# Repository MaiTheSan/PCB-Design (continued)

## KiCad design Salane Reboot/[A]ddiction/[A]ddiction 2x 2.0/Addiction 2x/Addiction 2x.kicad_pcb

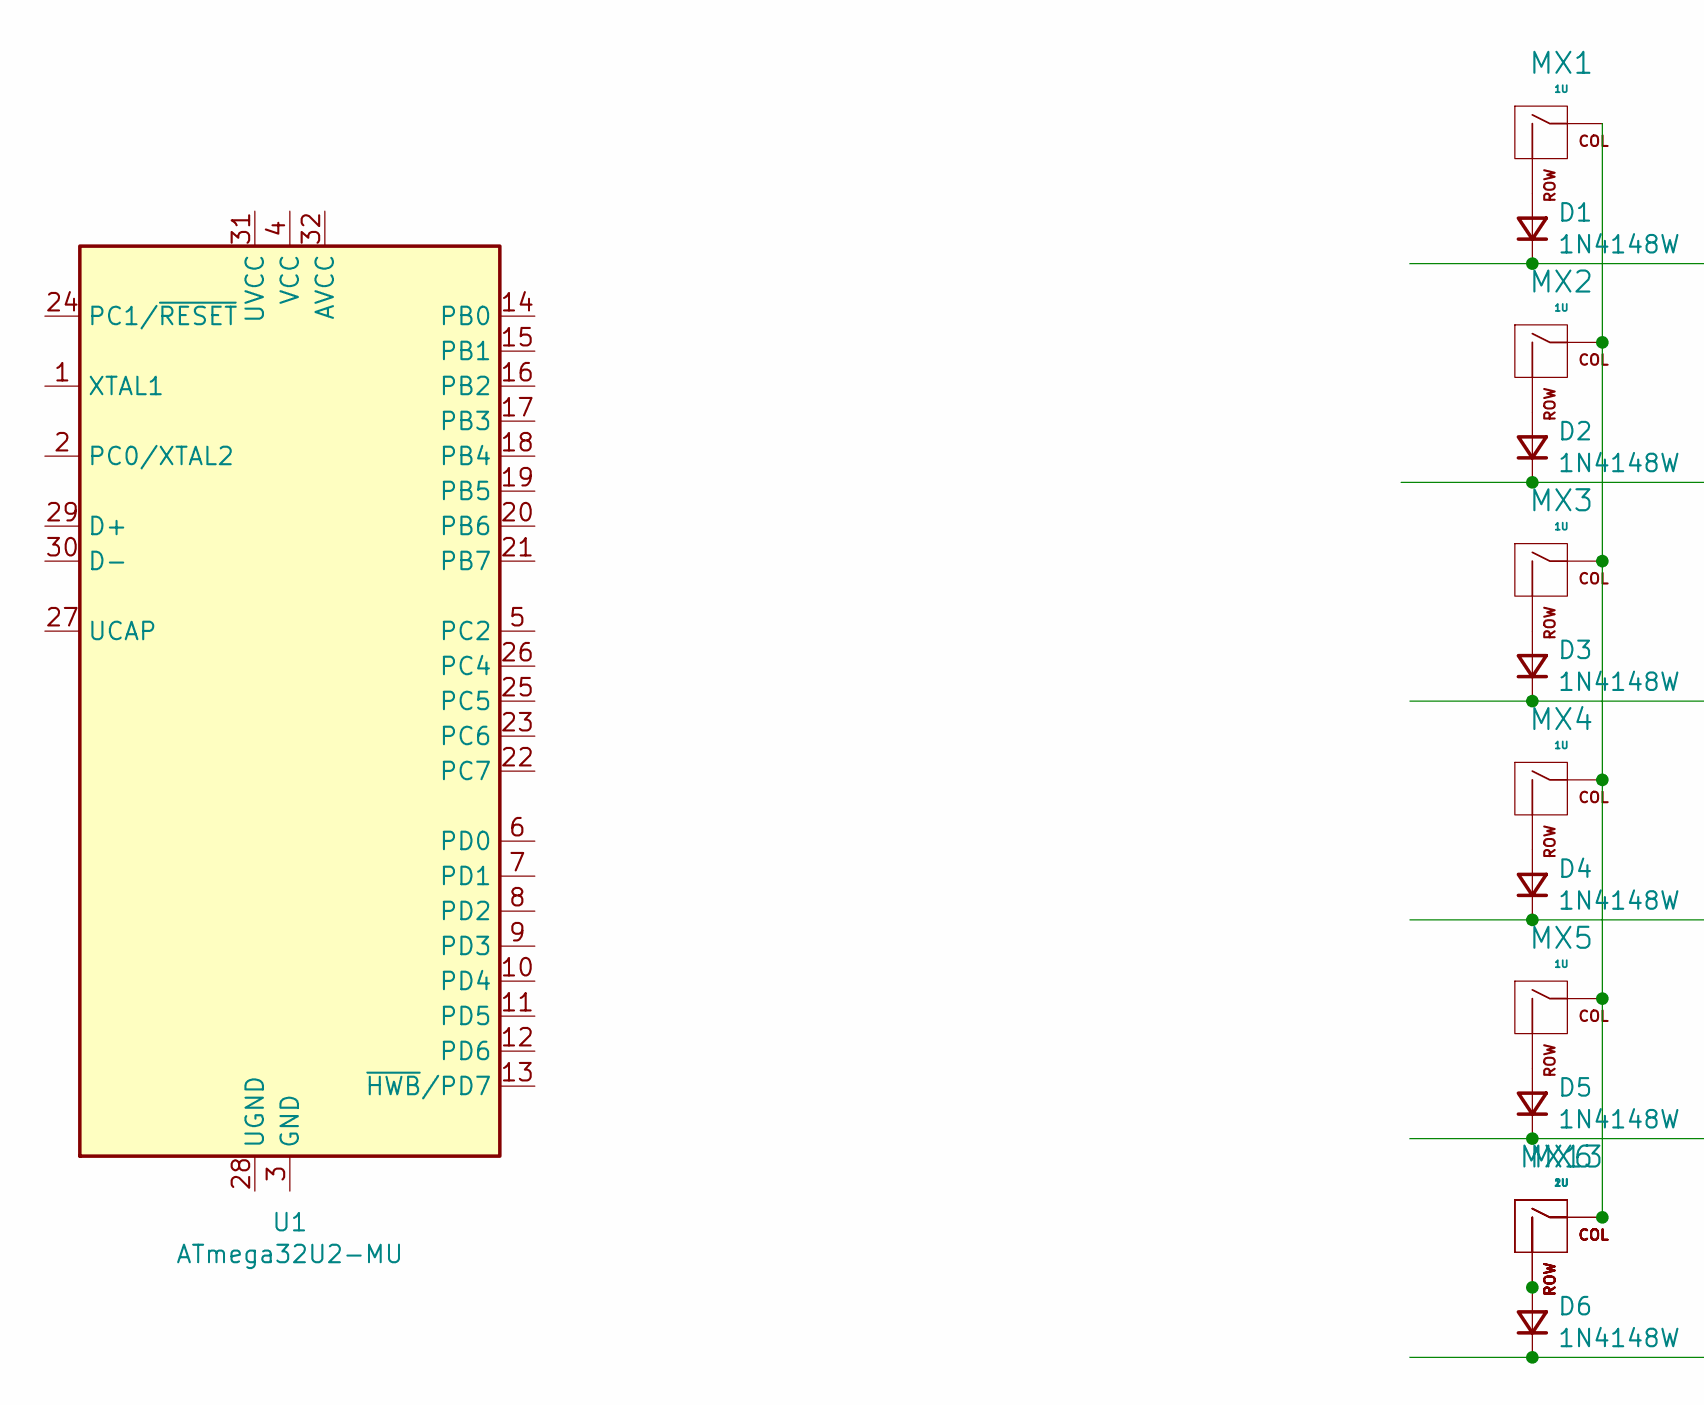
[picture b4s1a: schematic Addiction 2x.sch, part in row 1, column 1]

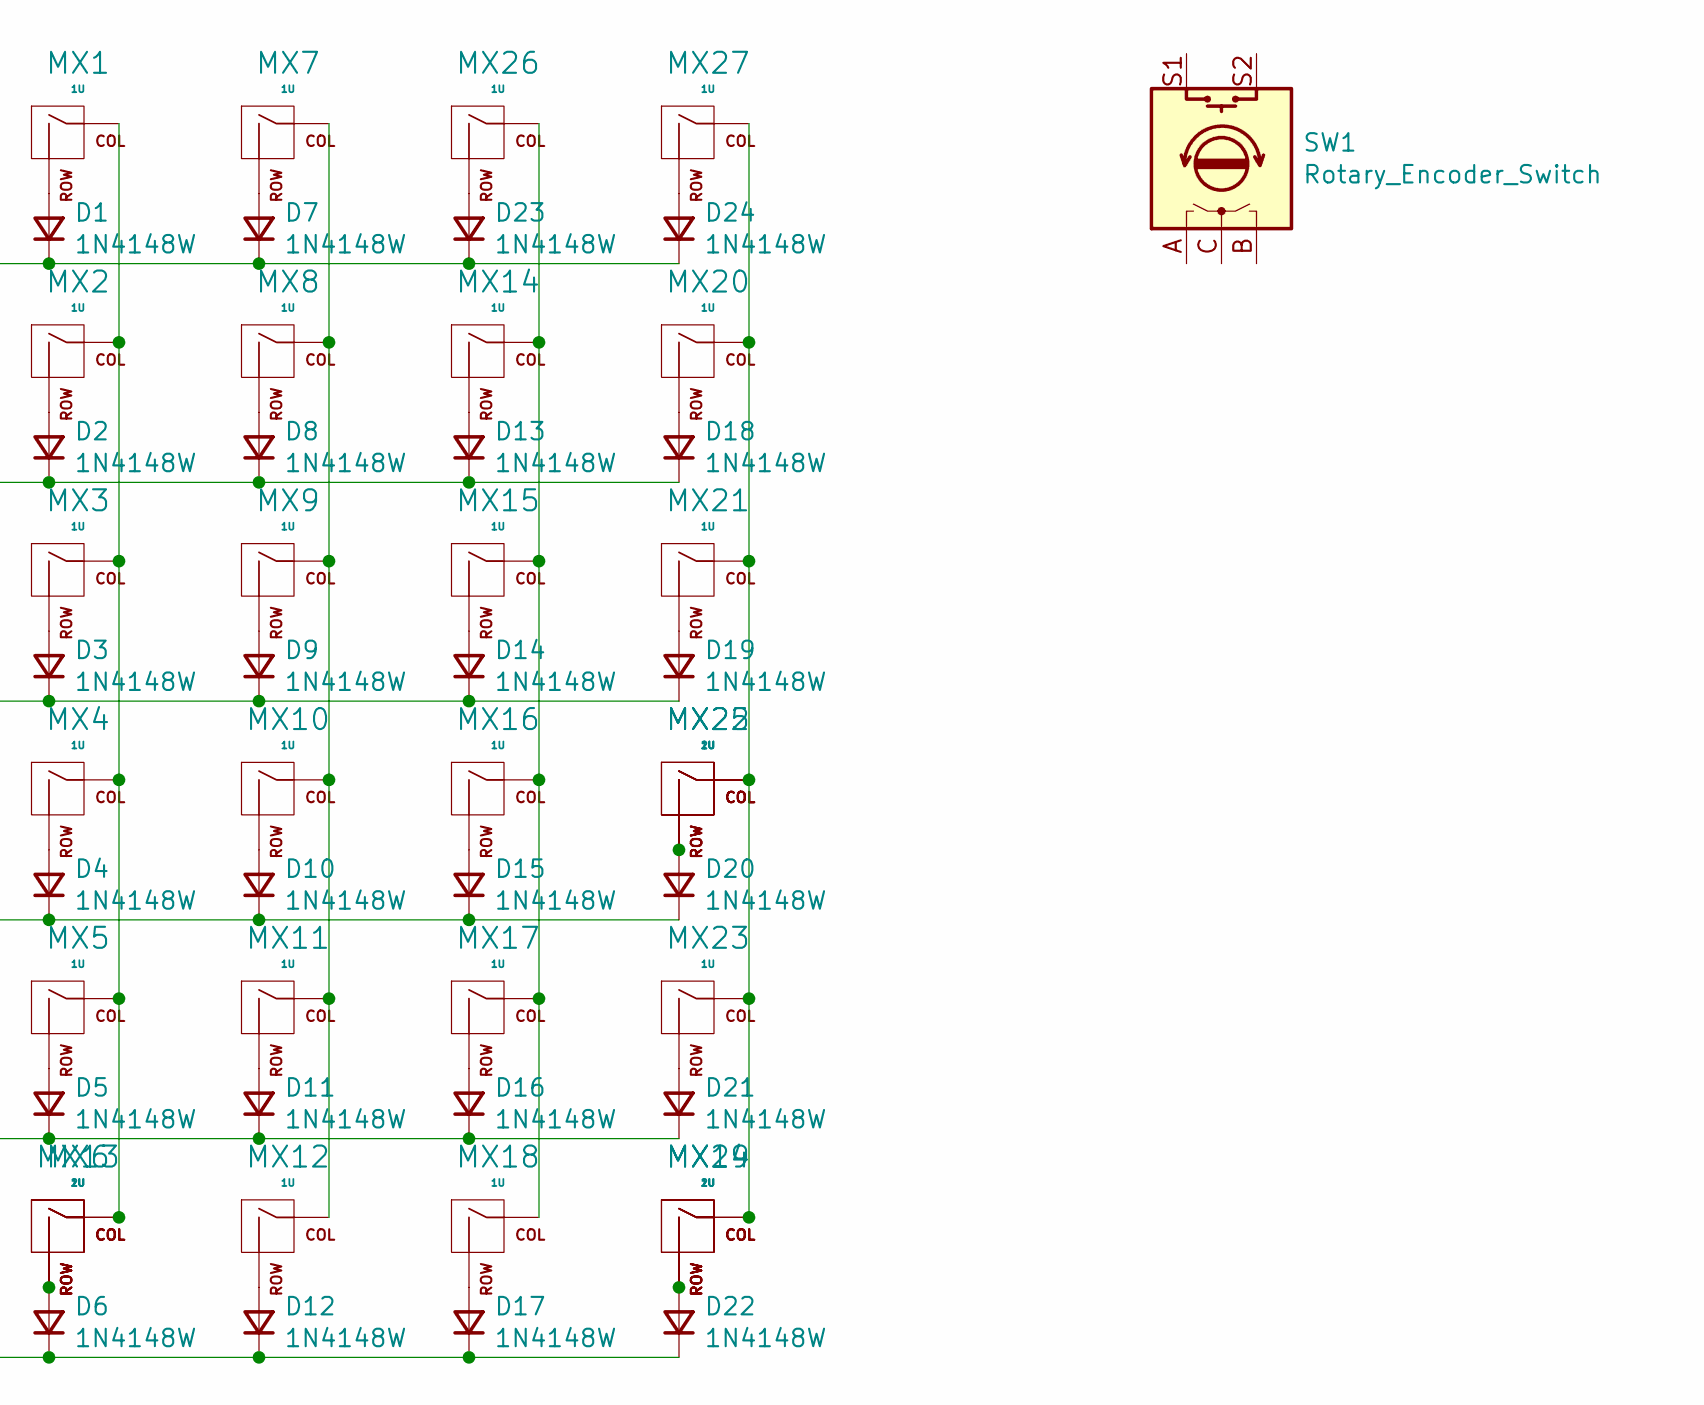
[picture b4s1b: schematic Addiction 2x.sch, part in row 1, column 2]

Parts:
D1, D2, D3, D4, D5, D6, D7, D8, D9, D10, D11, D12, D13, D14, D15, D16, D17, D18, D19, D20, D21, D22, D23, D24: 1N4148W; DIODE_1206_SawnsProjects
MX1, MX2, MX3, MX4, MX5, MX6, MX7, MX8, MX9, MX10, MX11, MX12, MX14, MX15, MX16, MX17, MX18, MX20, MX21, MX22, MX23, MX24, MX26, MX27: 1U; MXOnly-1U-NoLED
MX13, MX19, MX25: 2U; MXOnly-2U-ReversedStabilizers-NoLED
SW1: Rotary_Encoder_Switch; RotaryEncoder_Alps_EC11E-Switch_Vertical_H20mm_Center
U1: ATmega32U2-MU; QFN-32-1EP_5x5mm_P0.5mm_EP3.1x3.1mm

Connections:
unnamed: D1.1 (K), D7.1 (K), D23.1 (K), D24.1 (K)
unnamed: D1.2 (A), MX1.2 (ROW)
unnamed: D2.2 (A), MX2.2 (ROW)
unnamed: D3.2 (A), MX3.2 (ROW)
unnamed: D4.2 (A), MX4.2 (ROW)
unnamed: D5.2 (A), MX5.2 (ROW)
unnamed: D6.2 (A), MX6.2 (ROW), MX13.2 (ROW)
unnamed: D7.2 (A), MX7.2 (ROW)
unnamed: D8.2 (A), MX8.2 (ROW)
unnamed: D9.2 (A), MX9.2 (ROW)
unnamed: D4.1 (K), D10.1 (K), D15.1 (K), D20.1 (K)
unnamed: D10.2 (A), MX10.2 (ROW)
unnamed: D5.1 (K), D11.1 (K), D16.1 (K), D21.1 (K)
unnamed: D11.2 (A), MX11.2 (ROW)
unnamed: D6.1 (K), D12.1 (K), D17.1 (K), D22.1 (K)
unnamed: D12.2 (A), MX12.2 (ROW)
unnamed: D2.1 (K), D8.1 (K), D13.1 (K), D18.1 (K)
unnamed: D13.2 (A), MX14.2 (ROW)
unnamed: D3.1 (K), D9.1 (K), D14.1 (K), D19.1 (K)
unnamed: D14.2 (A), MX15.2 (ROW)
unnamed: D15.2 (A), MX16.2 (ROW)
unnamed: D16.2 (A), MX17.2 (ROW)
unnamed: D17.2 (A), MX18.2 (ROW)
unnamed: D18.2 (A), MX20.2 (ROW)
unnamed: D19.2 (A), MX21.2 (ROW)
unnamed: D20.2 (A), MX22.2 (ROW), MX25.2 (ROW)
unnamed: D21.2 (A), MX23.2 (ROW)
unnamed: D22.2 (A), MX19.2 (ROW), MX24.2 (ROW)
unnamed: D23.2 (A), MX26.2 (ROW)
unnamed: D24.2 (A), MX27.2 (ROW)
unnamed: MX1.1 (COL), MX2.1 (COL), MX3.1 (COL), MX4.1 (COL), MX5.1 (COL), MX6.1 (COL), MX13.1 (COL)
unnamed: MX7.1 (COL), MX8.1 (COL), MX9.1 (COL), MX10.1 (COL), MX11.1 (COL), MX12.1 (COL)
unnamed: MX14.1 (COL), MX15.1 (COL), MX16.1 (COL), MX17.1 (COL), MX18.1 (COL), MX26.1 (COL)
unnamed: MX19.1 (COL), MX20.1 (COL), MX21.1 (COL), MX22.1 (COL), MX23.1 (COL), MX24.1 (COL), MX25.1 (COL), MX27.1 (COL)
unnamed: U1.3 (GND), U1.33 (GND)

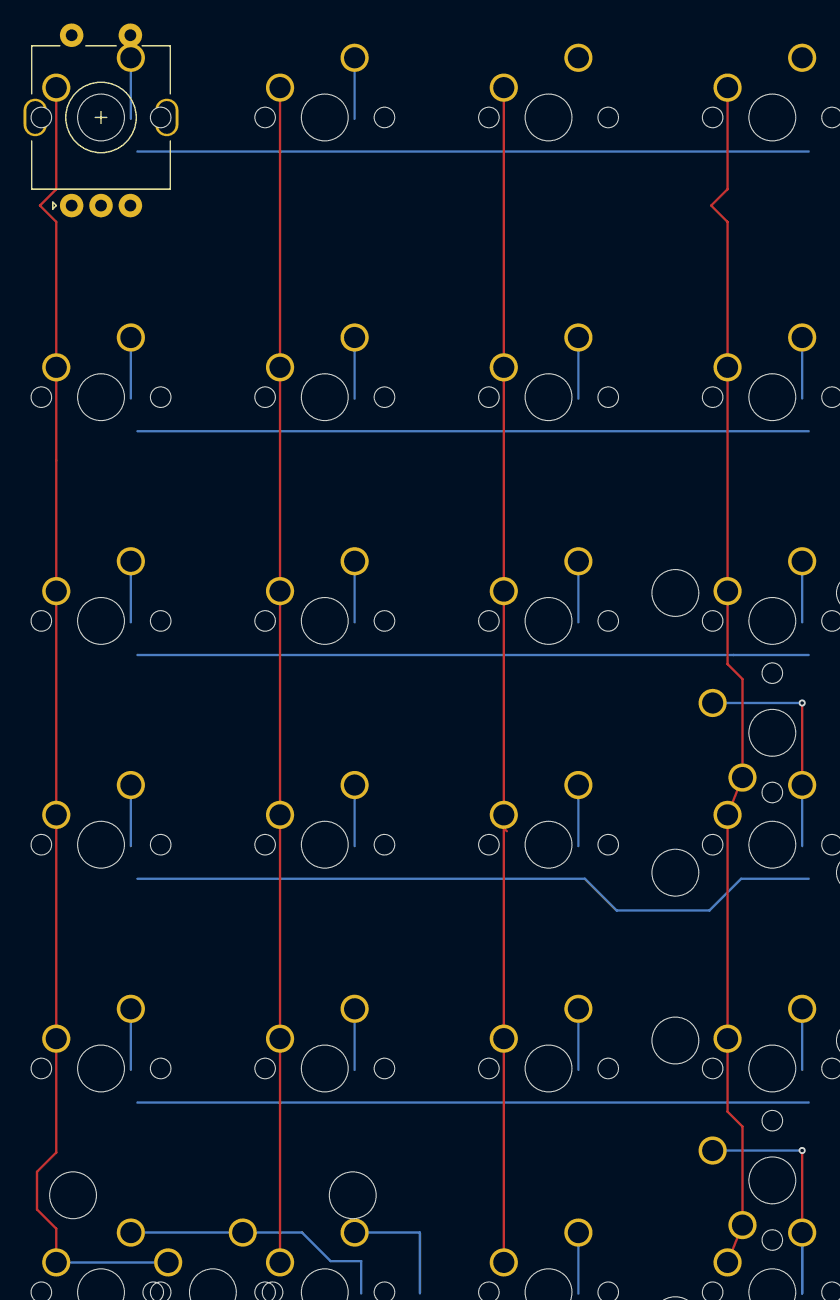
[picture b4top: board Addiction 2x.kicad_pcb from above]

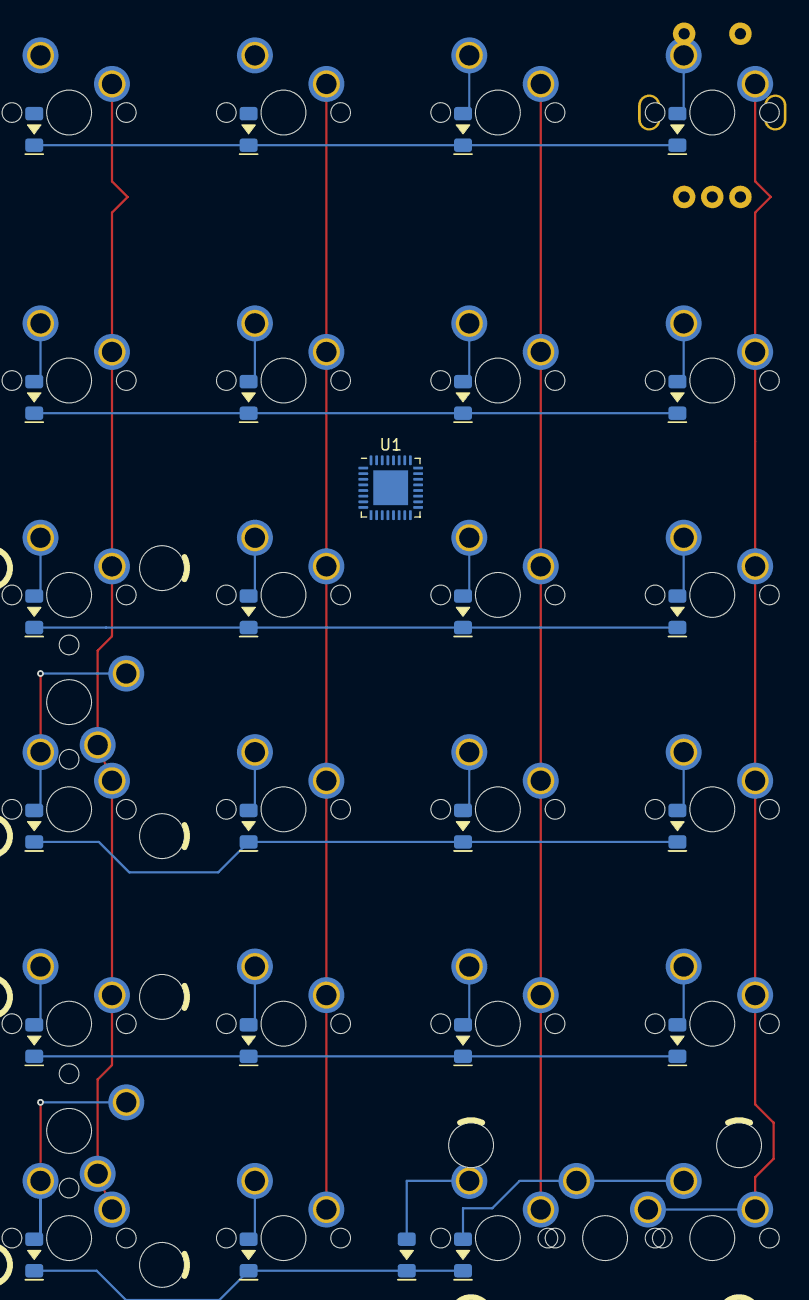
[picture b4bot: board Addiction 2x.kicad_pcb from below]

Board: 2 copper layers, 53 parts (25 on the bottom side), 35 nets.

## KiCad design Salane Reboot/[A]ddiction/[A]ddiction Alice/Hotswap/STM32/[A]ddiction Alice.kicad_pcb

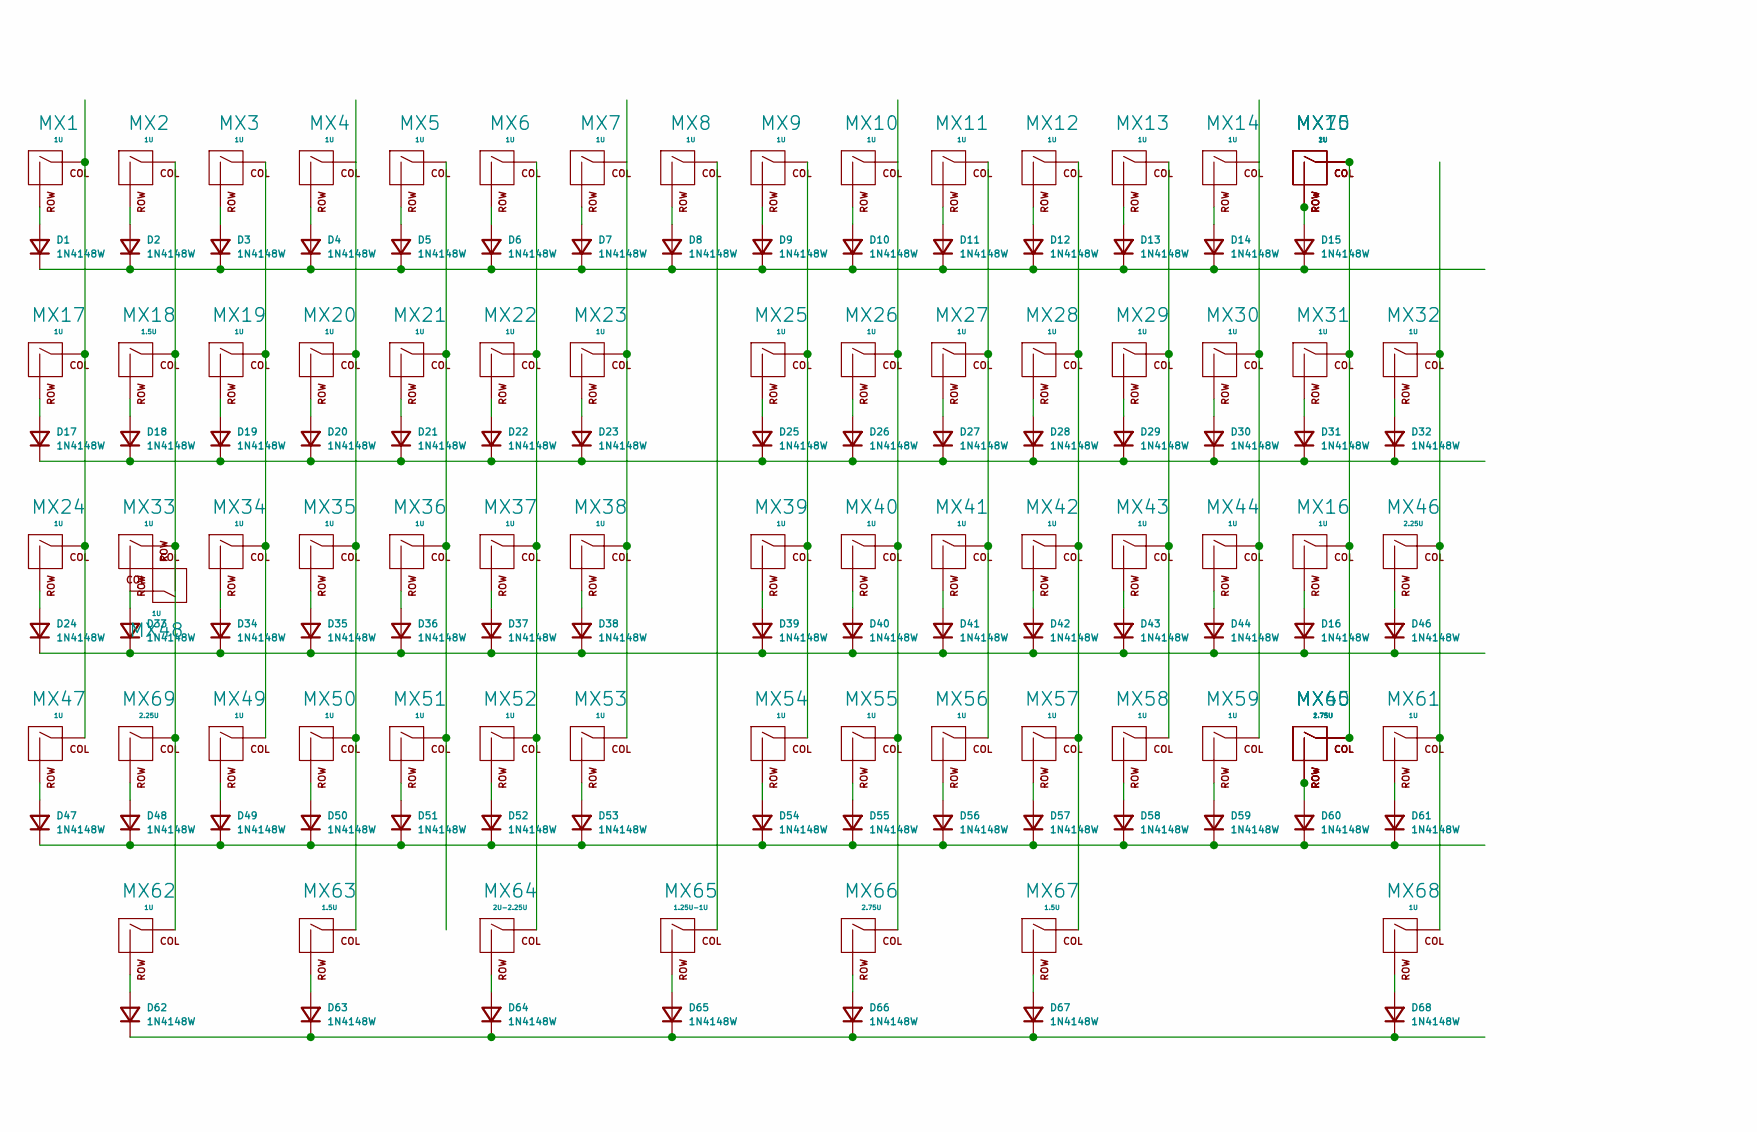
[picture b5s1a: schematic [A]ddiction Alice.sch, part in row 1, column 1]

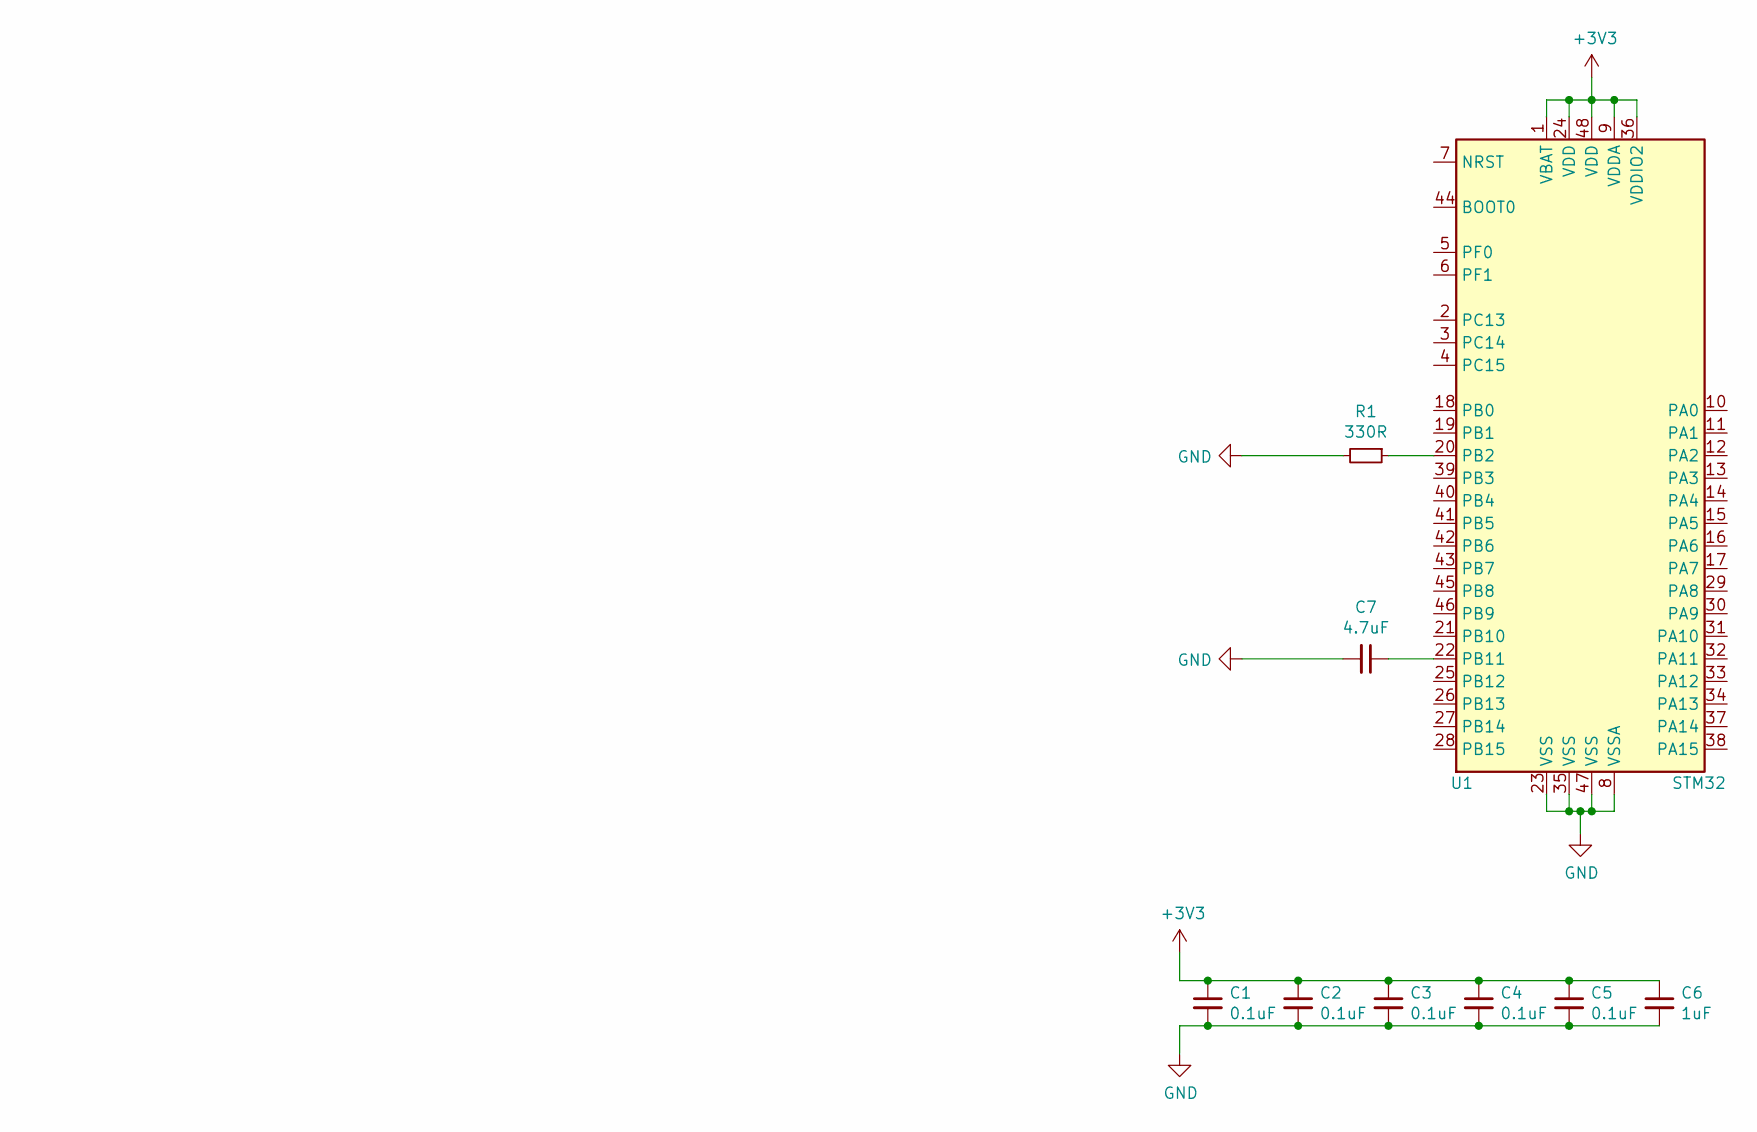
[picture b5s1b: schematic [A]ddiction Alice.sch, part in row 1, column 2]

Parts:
C1, C2, C3, C4, C5: 0.1uF; C_0402
C6: 1uF; C_0402
C7: 4.7uF; C_0402
D1, D2, D3, D4, D5, D6, D7, D8, D9, D10, D11, D12, D13, D14, D15, D16, D17, D18, D19, D20, D21, D22, D23, D24, D25, D26, D27, D28, D29, D30, D31, D32, D33, D34, D35, D36, D37, D38, D39, D40, D41, D42, D43, D44, D46, D47, D48, D49, D50, D51, D52, D53, D54, D55, D56, D57, D58, D59, D60, D61, D62, D63, D64, D65, D66, D67, D68: 1N4148W; DIODE_1206_SawnsProjects
MX1, MX2, MX3, MX4, MX5, MX6, MX7, MX8, MX9, MX10, MX11, MX12, MX13, MX14, MX15, MX16, MX17, MX19, MX20, MX21, MX22, MX23, MX24, MX25, MX26, MX27, MX28, MX29, MX30, MX31, MX32, MX33, MX34, MX35, MX36, MX37, MX38, MX39, MX40, MX41, MX42, MX43, MX44, MX47, MX48, MX49, MX50, MX51, MX52, MX53, MX54, MX55, MX56, MX57, MX58, MX59, MX61, MX62, MX68: 1U; MXOnly-1U-Hotswap-Sawns
MX18, MX63, MX67: 1.5U; MXOnly-1.5U-Hotswap-Sawns
MX45: 2.75U; MXOnly-2.75U-Hotswap-Sawns
MX46: 2.25U; MXOnly-2.25U-Hotswap-ReversedStabilizers-Sawns
MX60: 1.75U; MXOnly-1.75U-Hotswap-Sawns
MX64: 2U-2.25U; MXOnly-2U-2.25U-ReversedStabilizers-NoLED
MX65: 1.25U-1U; MXOnly-1.25U-1U-NoLED
MX66: 2.75U; MXOnly-2.75U-Hotswap-ReversedStabilizers-Sawns
MX69: 2.25U; MXOnly-2.25U-Hotswap-Sawns
MX70: 2U; MXOnly-2U-Hotswap-Sawns
R1: 330R; R_0402_1005Metric
U1: STM32; LQFP-48_7x7mm_P0.5mm

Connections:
+3V3: C1.1, C2.1, C3.1, C4.1, C5.1, C6.1, U1.1 (VBAT), U1.9 (VDDA), U1.24 (VDD), U1.36 (VDDIO2), U1.48 (VDD)
GND: C1.2, C2.2, C3.2, C4.2, C5.2, C6.2, C7.2, R1.2, U1.8 (VSSA), U1.23 (VSS), U1.35 (VSS), U1.47 (VSS); also elsewhere on the board
unnamed: C7.1, U1.22 (PB11)
unnamed: D1.1 (K), D2.1 (K), D3.1 (K), D4.1 (K), D5.1 (K), D6.1 (K), D7.1 (K), D8.1 (K), D9.1 (K), D10.1 (K), D11.1 (K), D12.1 (K), D13.1 (K), D14.1 (K), D15.1 (K)
unnamed: D1.2 (A), MX1.2 (ROW)
unnamed: D2.2 (A), MX2.2 (ROW)
unnamed: D3.2 (A), MX3.2 (ROW)
unnamed: D4.2 (A), MX4.2 (ROW)
unnamed: D5.2 (A), MX5.2 (ROW)
unnamed: D6.2 (A), MX6.2 (ROW)
unnamed: D7.2 (A), MX7.2 (ROW)
unnamed: D8.2 (A), MX8.2 (ROW)
unnamed: D9.2 (A), MX9.2 (ROW)
unnamed: D10.2 (A), MX10.2 (ROW)
unnamed: D11.2 (A), MX11.2 (ROW)
unnamed: D12.2 (A), MX12.2 (ROW)
unnamed: D13.2 (A), MX13.2 (ROW)
unnamed: D14.2 (A), MX14.2 (ROW)
unnamed: D15.2 (A), MX15.2 (ROW), MX70.2 (ROW)
unnamed: D16.1 (K), D24.1 (K), D33.1 (K), D34.1 (K), D35.1 (K), D36.1 (K), D37.1 (K), D38.1 (K), D39.1 (K), D40.1 (K), D41.1 (K), D42.1 (K), D43.1 (K), D44.1 (K), D46.1 (K)
unnamed: D16.2 (A), MX16.2 (ROW)
unnamed: D17.1 (K), D18.1 (K), D19.1 (K), D20.1 (K), D21.1 (K), D22.1 (K), D23.1 (K), D25.1 (K), D26.1 (K), D27.1 (K), D28.1 (K), D29.1 (K), D30.1 (K), D31.1 (K), D32.1 (K)
unnamed: D17.2 (A), MX17.2 (ROW)
unnamed: D18.2 (A), MX18.2 (ROW)
unnamed: D19.2 (A), MX19.2 (ROW)
unnamed: D20.2 (A), MX20.2 (ROW)
unnamed: D21.2 (A), MX21.2 (ROW)
unnamed: D22.2 (A), MX22.2 (ROW)
unnamed: D23.2 (A), MX23.2 (ROW)
unnamed: D24.2 (A), MX24.2 (ROW)
unnamed: D25.2 (A), MX25.2 (ROW)
unnamed: D26.2 (A), MX26.2 (ROW)
unnamed: D27.2 (A), MX27.2 (ROW)
unnamed: D28.2 (A), MX28.2 (ROW)
unnamed: D29.2 (A), MX29.2 (ROW)
unnamed: D30.2 (A), MX30.2 (ROW)
unnamed: D31.2 (A), MX31.2 (ROW)
unnamed: D32.2 (A), MX32.2 (ROW)
unnamed: D33.2 (A), MX33.2 (ROW), MX48.1 (COL)
unnamed: D34.2 (A), MX34.2 (ROW)
unnamed: D35.2 (A), MX35.2 (ROW)
unnamed: D36.2 (A), MX36.2 (ROW)
unnamed: D37.2 (A), MX37.2 (ROW)
unnamed: D38.2 (A), MX38.2 (ROW)
unnamed: D39.2 (A), MX39.2 (ROW)
unnamed: D40.2 (A), MX40.2 (ROW)
unnamed: D41.2 (A), MX41.2 (ROW)
unnamed: D42.2 (A), MX42.2 (ROW)
unnamed: D43.2 (A), MX43.2 (ROW)
unnamed: D44.2 (A), MX44.2 (ROW)
unnamed: D46.2 (A), MX46.2 (ROW)
unnamed: D47.1 (K), D48.1 (K), D49.1 (K), D50.1 (K), D51.1 (K), D52.1 (K), D53.1 (K), D54.1 (K), D55.1 (K), D56.1 (K), D57.1 (K), D58.1 (K), D59.1 (K), D60.1 (K), D61.1 (K)
unnamed: D47.2 (A), MX47.2 (ROW)
unnamed: D48.2 (A), MX69.2 (ROW)
unnamed: D49.2 (A), MX49.2 (ROW)
unnamed: D50.2 (A), MX50.2 (ROW)
unnamed: D51.2 (A), MX51.2 (ROW)
unnamed: D52.2 (A), MX52.2 (ROW)
unnamed: D53.2 (A), MX53.2 (ROW)
unnamed: D54.2 (A), MX54.2 (ROW)
unnamed: D55.2 (A), MX55.2 (ROW)
unnamed: D56.2 (A), MX56.2 (ROW)
unnamed: D57.2 (A), MX57.2 (ROW)
unnamed: D58.2 (A), MX58.2 (ROW)
unnamed: D59.2 (A), MX59.2 (ROW)
unnamed: D60.2 (A), MX45.2 (ROW), MX60.2 (ROW)
unnamed: D61.2 (A), MX61.2 (ROW)
unnamed: D62.1 (K), D63.1 (K), D64.1 (K), D65.1 (K), D66.1 (K), D67.1 (K), D68.1 (K)
unnamed: D62.2 (A), MX62.2 (ROW)
unnamed: D63.2 (A), MX63.2 (ROW)
unnamed: D64.2 (A), MX64.2 (ROW)
unnamed: D65.2 (A), MX65.2 (ROW)
unnamed: D66.2 (A), MX66.2 (ROW)
unnamed: D67.2 (A), MX67.2 (ROW)
unnamed: D68.2 (A), MX68.2 (ROW)
unnamed: MX1.1 (COL), MX17.1 (COL), MX24.1 (COL), MX47.1 (COL)
unnamed: MX10.1 (COL), MX26.1 (COL), MX40.1 (COL), MX55.1 (COL), MX66.1 (COL)
unnamed: MX11.1 (COL), MX27.1 (COL), MX41.1 (COL), MX56.1 (COL)
unnamed: MX12.1 (COL), MX28.1 (COL), MX42.1 (COL), MX57.1 (COL), MX67.1 (COL)
unnamed: MX13.1 (COL), MX29.1 (COL), MX43.1 (COL), MX58.1 (COL)
unnamed: MX14.1 (COL), MX30.1 (COL), MX44.1 (COL), MX59.1 (COL)
unnamed: MX15.1 (COL), MX16.1 (COL), MX31.1 (COL), MX45.1 (COL), MX60.1 (COL), MX70.1 (COL)
unnamed: MX2.1 (COL), MX18.1 (COL), MX33.1 (COL), MX48.2 (ROW), MX62.1 (COL), MX69.1 (COL)
unnamed: MX3.1 (COL), MX19.1 (COL), MX34.1 (COL), MX49.1 (COL)
unnamed: MX4.1 (COL), MX20.1 (COL), MX35.1 (COL), MX50.1 (COL), MX63.1 (COL)
unnamed: MX5.1 (COL), MX21.1 (COL), MX36.1 (COL), MX51.1 (COL)
unnamed: MX6.1 (COL), MX22.1 (COL), MX37.1 (COL), MX52.1 (COL), MX64.1 (COL)
unnamed: MX7.1 (COL), MX23.1 (COL), MX38.1 (COL), MX53.1 (COL)
unnamed: MX9.1 (COL), MX25.1 (COL), MX39.1 (COL), MX54.1 (COL)
unnamed: MX32.1 (COL), MX46.1 (COL), MX61.1 (COL), MX68.1 (COL)
unnamed: MX8.1 (COL), MX65.1 (COL)
unnamed: R1.1, U1.20 (PB2)
unnamed 95: U1.5 (PF0); also elsewhere on the board
unnamed 96: U1.6 (PF1); also elsewhere on the board

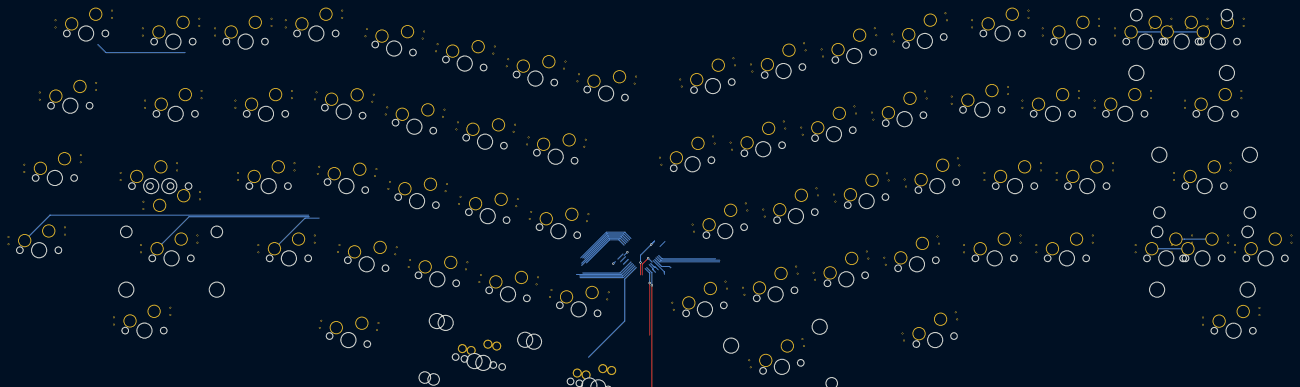
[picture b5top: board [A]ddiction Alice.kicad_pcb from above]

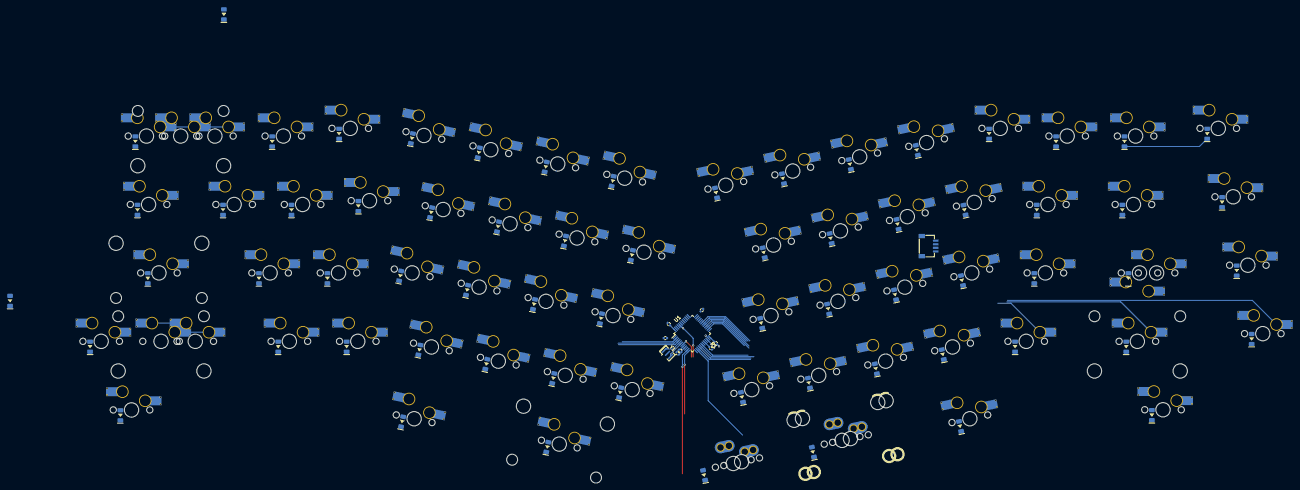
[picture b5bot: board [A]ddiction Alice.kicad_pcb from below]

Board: 2 copper layers, 148 parts (78 on the bottom side), 94 nets.

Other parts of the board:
J1: Conn_01x04_Female; JST-SR-4
Y1: 8Mhz; Resonator_SMD_muRata_CSTxExxV-3Pin_3.0x1.1mm

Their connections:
GND: Y1.2; also elsewhere on the board
unnamed 95: Y1.1; also elsewhere on the board
unnamed 96: Y1.3; also elsewhere on the board
